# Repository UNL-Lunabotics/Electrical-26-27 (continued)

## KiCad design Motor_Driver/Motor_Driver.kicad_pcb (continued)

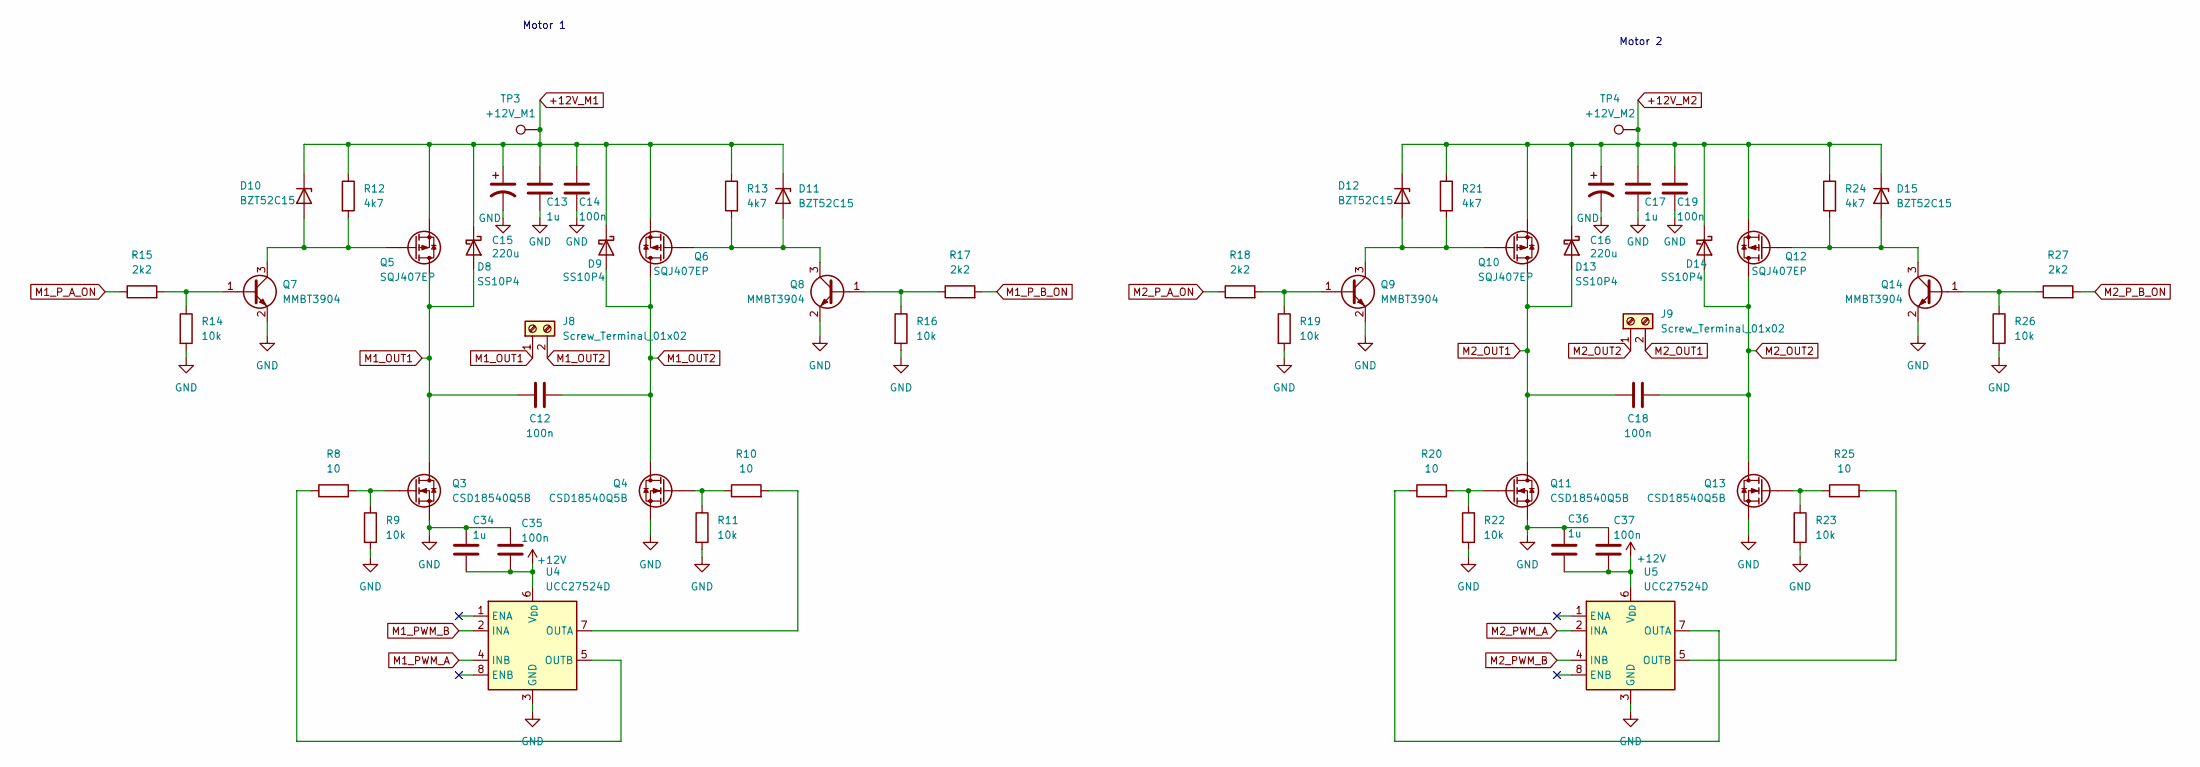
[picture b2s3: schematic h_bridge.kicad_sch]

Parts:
C12, C14, C18, C19, C35, C37: 100n; C_0805_2012Metric
C13, C17, C34, C36: 1u; C_0805_2012Metric
C15, C16: 220u; CP_Elec_8x10.5; Digikey_ID 25SKV220M8X10.5
D8, D9, D13, D14: SS10P4; TO-277A_SS10P4_K-tab; Digikey_ID SS10P4-M3/86A
D10, D11, D12, D15: BZT52C15; D_SOD-123; Digikey_ID BZT52C15-E3-08
J8, J9: Screw_Terminal_01x02; TerminalBlock_MaiXu_MX126-5.0-02P_1x02_P5.00mm; Digikey_ID 1729128
Q3, Q4, Q11, Q13: CSD18540Q5B; TDSON-8-1_SGD; Digikey_ID CSD18532Q5B
Q5, Q6, Q10, Q12: SQJ407EP; PowerPAK_SO-8_Single_SGD; Digikey_ID SQJ407EP-T1_GE3
Q7, Q8, Q9, Q14: MMBT3904; SOT-23; Digikey_ID MMBT3904LT1G
R8, R10, R20, R25: 10; R_0805_2012Metric; Digikey_ID RC0805FR-0710RL
R9, R11, R14, R16, R19, R22, R23, R26: 10k; R_0805_2012Metric
R12, R13, R21, R24: 4k7; R_0805_2012Metric
R15, R17, R18, R27: 2k2; R_0805_2012Metric; Digikey_ID RC0805FR-072K2L
TP3: +12V_M1; TestPoint_Pad_D1.5mm
TP4: +12V_M2; TestPoint_Pad_D1.5mm
U4, U5: UCC27524D; SOIC-8_3.9x4.9mm_P1.27mm; Digikey_ID UCC27524D

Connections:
+12V: C34.2, C35.2, C36.2, C37.2, U4.6 (V_{DD}), U5.6 (V_{DD}); also elsewhere on the board
+12V_M1: C13.1, C14.1, C15.1, D8.1 (K), D9.1 (K), D10.1 (K), D11.1 (K), Q5.S, Q6.S, R12.1, R13.1, TP3.1 (1_1); also elsewhere on the board
+12V_M2: C16.1, C17.1, C19.1, D12.1 (K), D13.1 (K), D14.1 (K), D15.1 (K), Q10.S, Q12.S, R21.1, R24.1, TP4.1 (1_1); also elsewhere on the board
GND: C13.2, C14.2, C15.2, C16.2, C17.2, C19.2, C34.1, C35.1, C36.1, C37.1, Q3.S, Q4.S, Q7.2 (E), Q8.2 (E), Q9.2 (E), Q11.S, Q13.S, Q14.2 (E), R9.2, R11.2, R14.2, R16.2, R19.2, R22.2, R23.2, R26.2, U4.3 (GND), U5.3 (GND); also elsewhere on the board
M1_OUT1: C12.1, D8.2 (A), J8.1, Q3.D, Q5.D
M1_OUT2: C12.2, D9.2 (A), J8.2, Q4.D, Q6.D
M1_PWM_A: U4.4 (INB); also elsewhere on the board
M1_PWM_B: U4.2 (INA); also elsewhere on the board
M1_P_A_ON: R15.1; also elsewhere on the board
M1_P_B_ON: R17.2; also elsewhere on the board
M2_OUT1: C18.1, D13.2 (A), J9.2, Q10.D, Q11.D
M2_OUT2: C18.2, D14.2 (A), J9.1, Q12.D, Q13.D
M2_PWM_A: U5.2 (INA); also elsewhere on the board
M2_PWM_B: U5.4 (INB); also elsewhere on the board
M2_P_A_ON: R18.1; also elsewhere on the board
M2_P_B_ON: R27.2; also elsewhere on the board
unnamed: D10.2 (A), Q5.G, Q7.3 (C), R12.2
unnamed: D11.2 (A), Q6.G, Q8.3 (C), R13.2
unnamed: D12.2 (A), Q9.3 (C), Q10.G, R21.2
unnamed: D15.2 (A), Q12.G, Q14.3 (C), R24.2
unnamed: Q3.G, R8.2, R9.1
unnamed: Q4.G, R10.1, R11.1
unnamed: Q7.1 (B), R14.1, R15.2
unnamed: Q8.1 (B), R16.1, R17.1
unnamed: Q9.1 (B), R18.2, R19.1
unnamed: Q11.G, R20.2, R22.1
unnamed: Q13.G, R23.1, R25.1
unnamed: Q14.1 (B), R26.1, R27.1
unnamed: R10.2, U4.7 (OUTA)
unnamed: R8.1, U4.5 (OUTB)
unnamed: R20.1, U5.7 (OUTA)
unnamed: R25.2, U5.5 (OUTB)

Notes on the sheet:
Motor 1
Motor 2

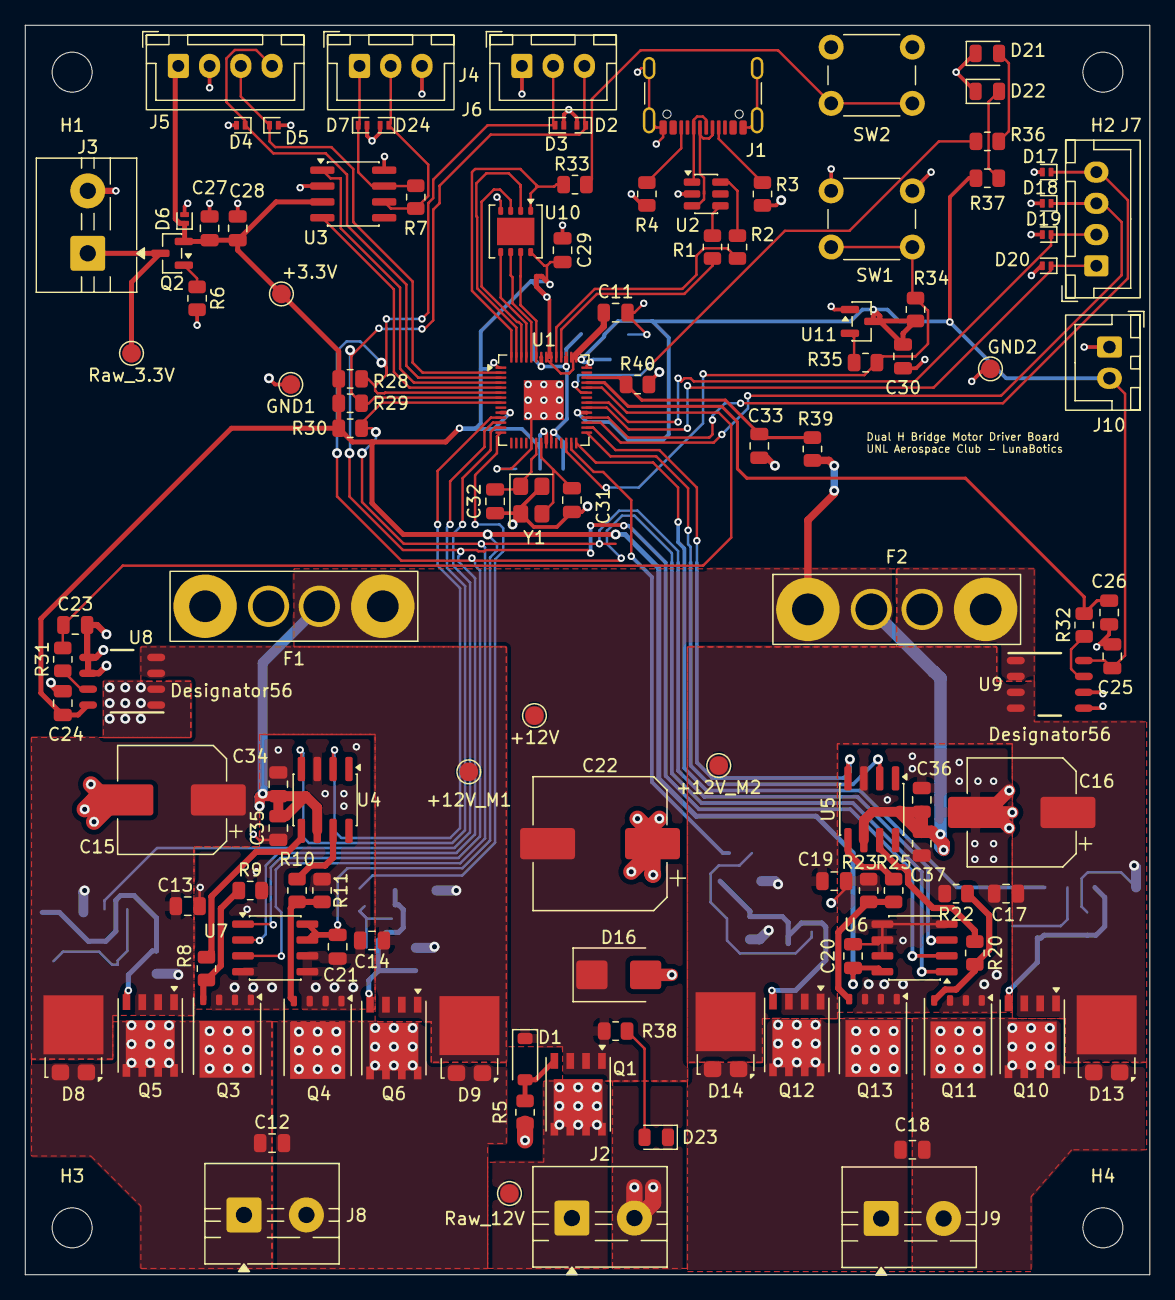
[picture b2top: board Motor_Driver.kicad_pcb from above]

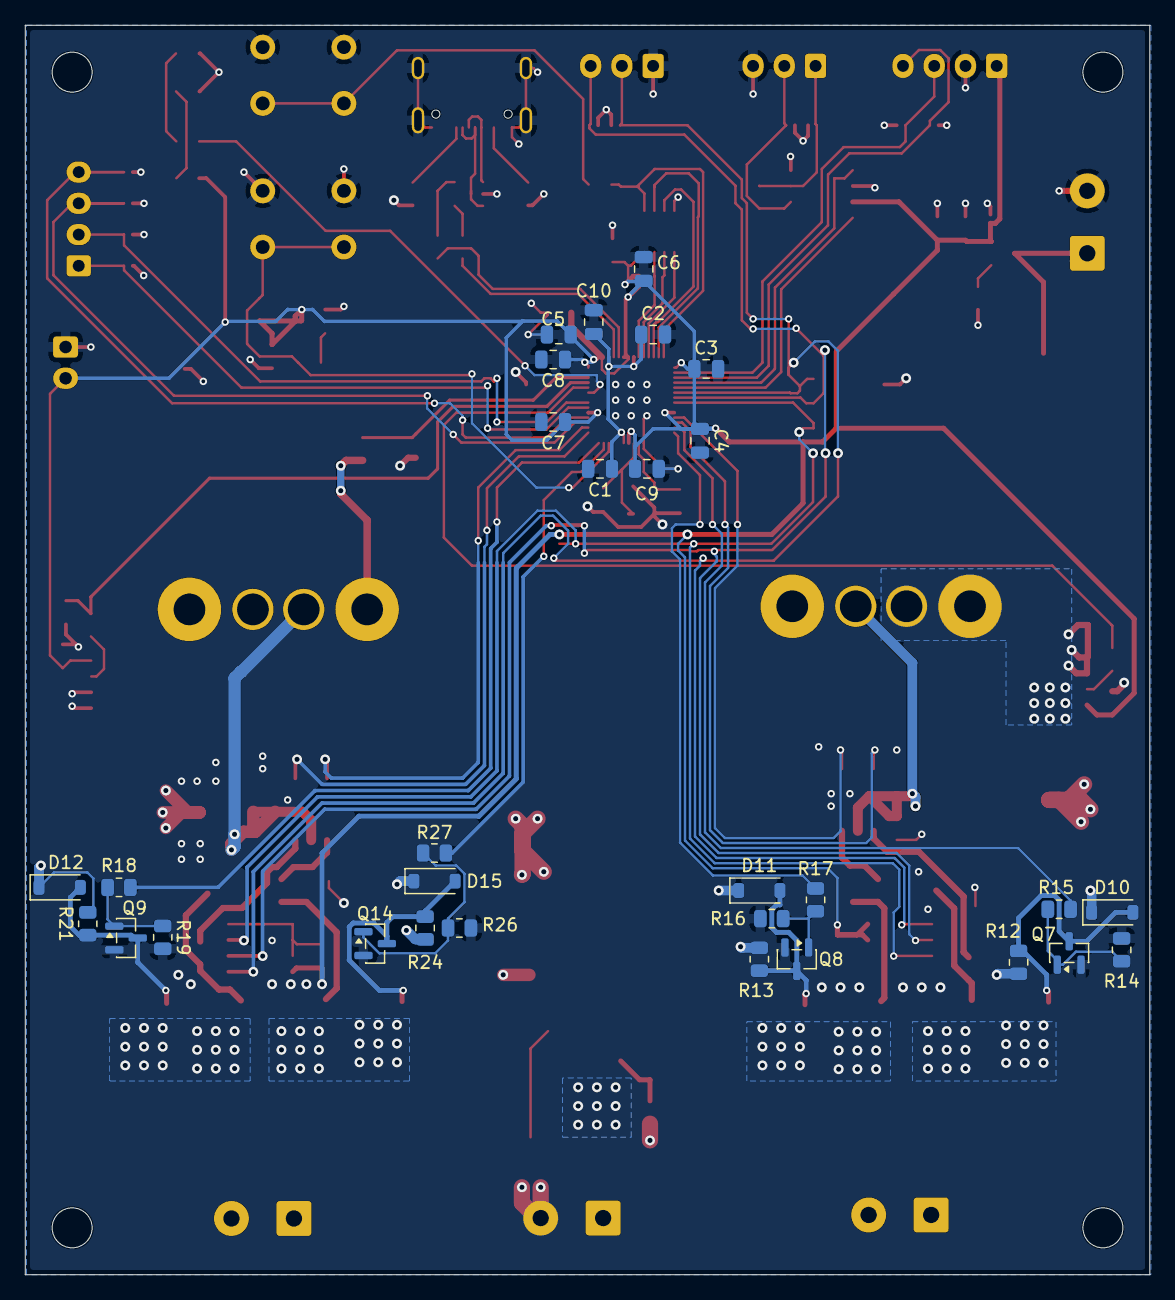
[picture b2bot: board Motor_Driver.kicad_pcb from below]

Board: 2 copper layers, 90.0 x 100.0 mm, 153 parts (30 on the bottom side), 81 nets.
